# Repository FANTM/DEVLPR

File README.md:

# DEVLPR

## About
 
[FANTM](https://getfantm.com) is creating easy-to-use EMG (muscle-based) interfaces for you and your computer. The DEVLPR is an Arduino shield that will make it so that you too can start playing around with EMG and all of the possibilities it opens up, whether it be for games, robotics, or something we've never thought of. Once we have the hardware in a functional state we plan on adding software libraries to make the device plug-and-play with Arduino and make it easy for the DEVLPR to be integrated into other projects. 

We're just two engineers who have a passion for new tech and Open Source, so share and build away!

## Disclaimer
This hardware is a major work in progress right now. We are still mid development cycle, and the board in its current state likely does not work. Once it is in a stable state we will tag a release but until then it's going to be frequently changing (and improving).

## Getting Started
This library relies on digikeys KiCAD symbol/footprint library, and they have been included as a submodule. This means when cloning with `git clone --recurse-submodules https://github.com/FANTM/DEVLPR`. If something goes wrong, the [git submodules documentation](https://git-scm.com/book/en/v2/Git-Tools-Submodules) is always helpful.

## License Information
This is an Open Source project and as such is licensed under CC. 

  <br />This work is licensed under a <a rel="license" href="http://creativecommons.org/licenses/by-sa/4.0/">Creative Commons Attribution-ShareAlike 4.0 International License</a>.

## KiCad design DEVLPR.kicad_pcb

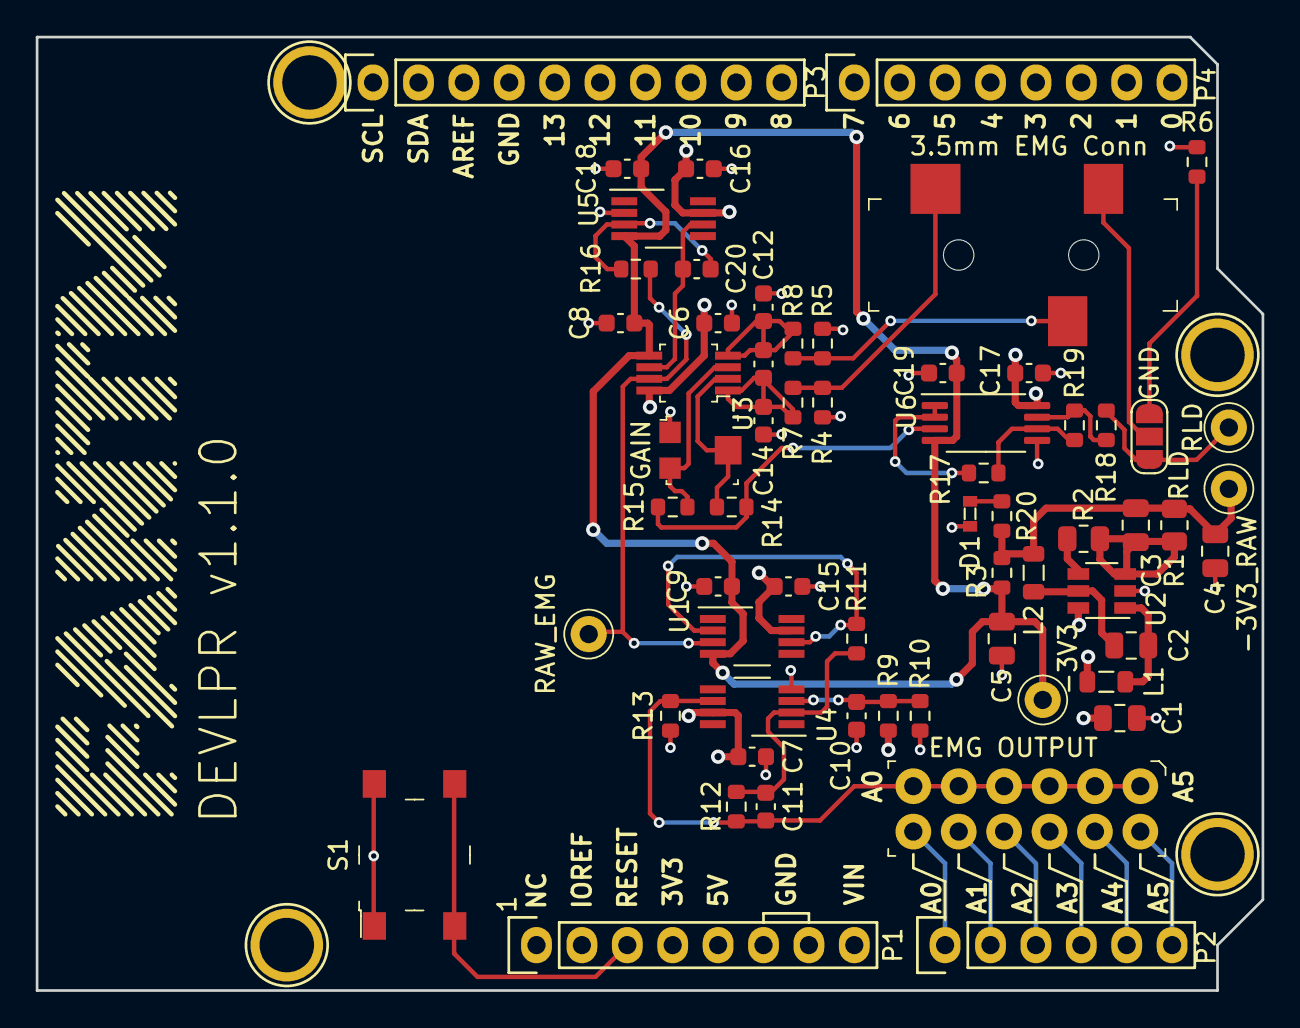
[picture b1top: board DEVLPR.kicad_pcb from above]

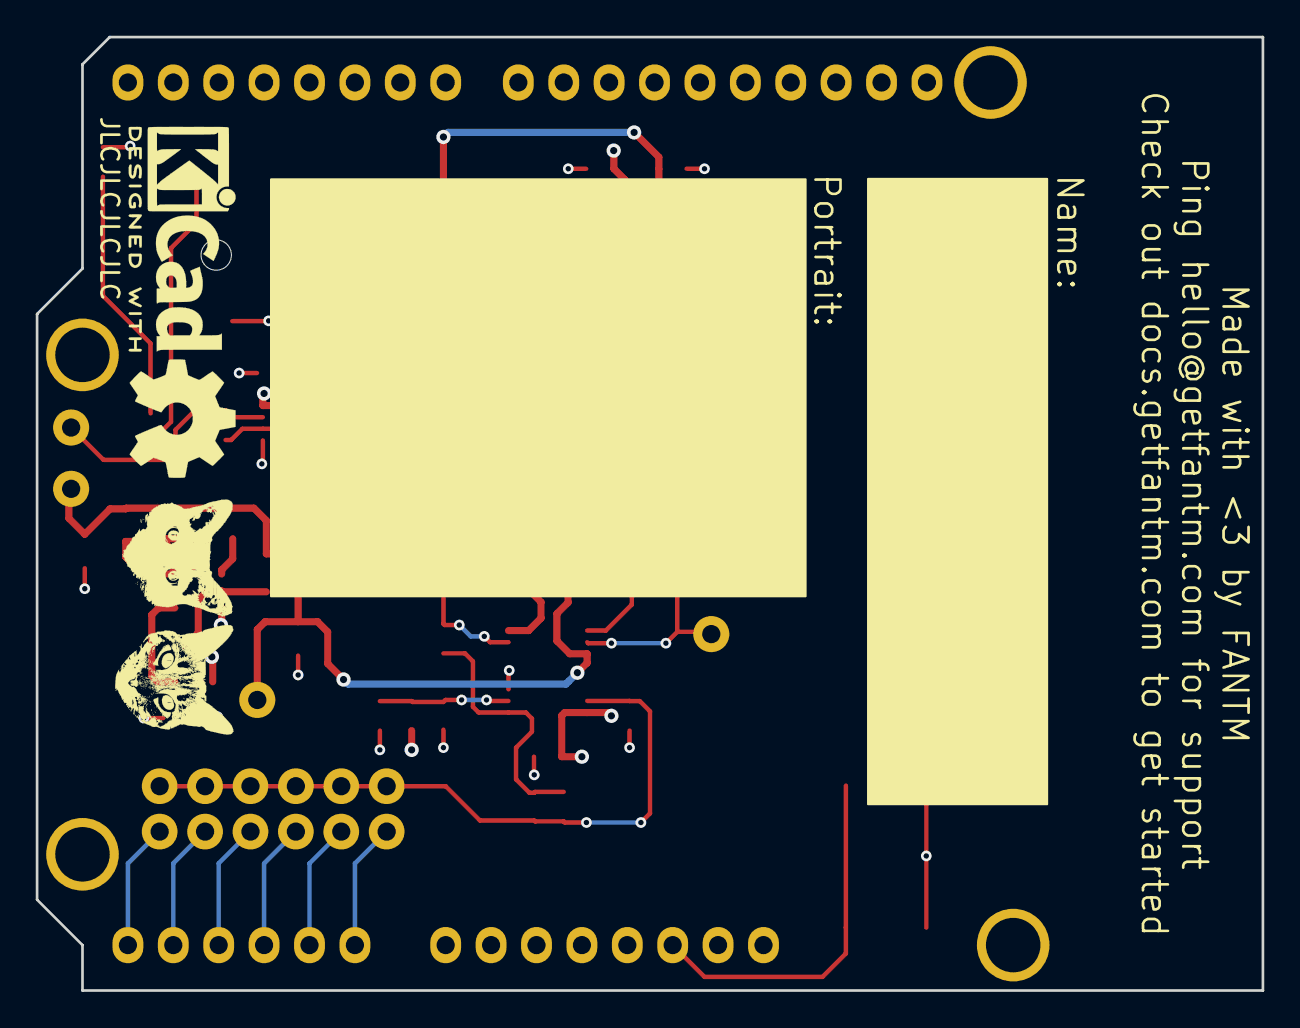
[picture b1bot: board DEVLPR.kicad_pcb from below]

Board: 4 copper layers, 68.6 x 53.3 mm, 72 parts (6 on the bottom side), 36 nets.

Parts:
C1, C2: 1uF; C_0805_2012Metric
C3: 22pF; C_0805_2012Metric
C4: 4.7uF; C_0805_2012Metric
C5: 10uF; C_0805_2012Metric
C6, C7, C8, C9, C15, C16, C17, C18, C19: 0.1uF; C_0603_1608Metric
C10, C20: 1uF; C_0603_1608Metric
C11: 4700pF; C_0603_1608Metric
C12, C14: 2.2pF; C_0603_1608Metric
C13: 10pF; C_0603_1608Metric
CON1: SJ-3523-SMT-TR; Switch_Slide_11.6x4mm_SJ-3523-SMT
D1: GREEN LED; 0603
J1: EMG OUTPUT; PinHeader_6x2_P2.54mm_Horizontal
JP1: RLD_SEL; SolderJumper-3_P1.3mm_Open_RoundedPad1.0x1.5mm_NumberLabels
L1, L2: 10uH; L_0805_2012Metric
P1: Power; Socket_Strip_Arduino_1x08
P2: Analog; Socket_Strip_Arduino_1x06
P3: Digital; Socket_Strip_Arduino_1x10
P4: Digital; Socket_Strip_Arduino_1x08
P5, P6, P7, P8: CONN_01X01; Arduino_1pin
POT1: GAIN; Trimpot_3.8mmx3.6mm_TC33X-2-103E
R1: 267k; R_0805_2012Metric
R2: 102k; R_0805_2012Metric
R3: 249; R_0603_1608Metric
R4, R5: 47k; R_0603_1608Metric
R6, R7, R8, R16, R18, R19: 100k; R_0603_1608Metric
R9: 68k; R_0603_1608Metric
R10, R11, R13, R17: 10k; R_0603_1608Metric
R12: 28.7k; R_0603_1608Metric
R14, R15: 470; R_0603_1608Metric
R20: 1k; R_0603_1608Metric
S1: PTS645SM43SMTR92_LFS; Switch_Tactile_SMD_6x6mm_PTS645
S2: Linus; linus_xsm
S3: Sinclair; sin_ham_bitmap_sm
S4: Kicad; KiCad-Logo2_5mm_SilkScreen
S5: OSHW; OSHW-Symbol_6.7x6mm_SilkScreen
S6: Portrait; portait
S7: Name; name
TP1: -3V3_RAW; Test_Point_D1.02mm
TP2: -3V3; Test_Point_D1.02mm
TP3: RAW_EMG; Test_Point_D1.02mm
TP4: RLD; Test_Point_D1.02mm
U1, U4, U5: OPA187IDR; VSSOP-8_3.0x3.0mm_P0.65mm
U2: LT3462A; TSOT-23-6
U3: INA821IDGKT; TSSOP-8_W3mm
U6: OPA2375IPWR; TSSOP-8_4.4x3mm_P0.65mm

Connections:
+3V3: C1.1, C6.2, C7.2, C15.2, C16.2, C17.2, L1.1, P1.4, R9.1, U1.7, U2.6, U3.8, U4.7, U5.7, U6.8
-3V3: C5.1, C8.2, C9.2, C18.2, C19.2, R3.1, TP2.1, U1.4, U3.5, U5.4, U6.4
/-3V3 Source/-3V3_D: C2.1, L2.1, U2.5
/-3V3 Source/-3V3_FB: C3.2, R1.2, R2.2, U2.3
/-3V3 Source/-3V3_RAW: C3.1, C4.1, L2.2, R1.1, R3.2, R20.1, TP1.1
/-3V3 Source/-3V3_SDREF: R2.1, U2.4
/-3V3 Source/-3V3_SW: C2.2, L1.2, U2.1
/A0: J1.12, P2.1
/A1: J1.10, P2.2
/A2: J1.8, P2.3
/A3: J1.6, P2.4
/A4(SDA): J1.4, P2.5
/A5(SCL): J1.2, P2.6
/EMG Amplifiers/BUFF_FDBK: R11.2, U1.2, U1.6
/EMG Amplifiers/BUFF_MID: C11.1, R11.1, R12.2, U4.2
/EMG Amplifiers/EMG_INSTR: R16.2, TP3.1, U1.3, U3.7
/EMG Amplifiers/GND_REF: JP1.3, R6.1
/EMG Amplifiers/INA_N: C13.1, C14.2, R7.2, U3.1
/EMG Amplifiers/INA_P: C12.1, C13.2, R8.2, U3.4
/EMG Amplifiers/INA_REF: C20.1, U3.6, U5.6
/EMG Amplifiers/REF_-: C20.2, R16.1, U5.3
/EMG Amplifiers/RG1: POT1.2, R14.2, U3.2
/EMG Amplifiers/RG2: POT1.3, R15.1, U3.3
/EMG Amplifiers/RLD: JP1.1, R18.2, TP4.1
/EMG Amplifiers/RLD_IN: R14.1, R15.2, U6.3
/EMG Amplifiers/RLD_IN2_-: R17.1, R19.2, U6.6
/EMG Amplifiers/RLD_MID: R17.2, U6.1, U6.2
/EMG Amplifiers/RLD_OUT2: R18.1, R19.1, U6.7
/EMG Amplifiers/V_SHIFT: C10.2, R9.2, R10.1, U4.3
/EMG_GND: CON1.1, JP1.2
/EMG_N: CON1.2, R4.2, R7.1
/EMG_OUT: C11.2, J1.1, J1.3, J1.5, J1.7, J1.9, J1.11, R12.1, R13.1, U4.6
/EMG_P: CON1.3, R5.2, R8.1
/Reset: P1.3, S1.3, S1.4
GND: C1.2, C4.2, C5.2, C6.1, C7.1, C8.1, C9.1, C10.1, C12.2, C14.1, C15.1, C16.1, C17.1, C18.1, C19.1, D1.1, P1.6, P1.7, P3.4, POT1.1, R4.1, R5.1, R6.2, R10.2, R13.2, S1.1, S1.2, U2.2, U4.4, U5.2, U6.5
unnamed: D1.2, R20.2

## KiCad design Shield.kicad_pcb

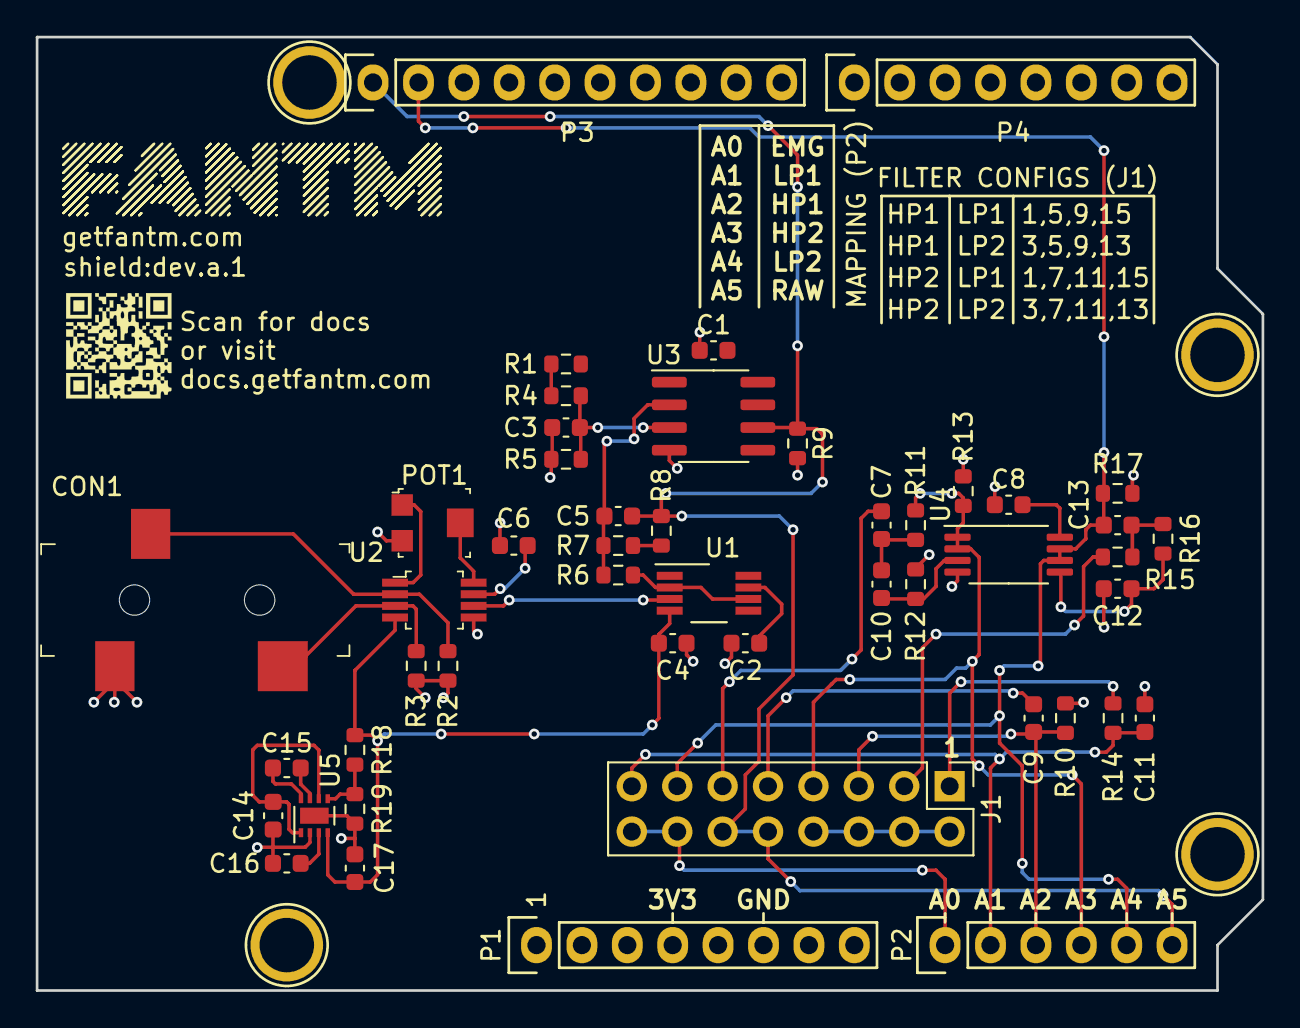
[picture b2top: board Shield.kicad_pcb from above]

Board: 2 copper layers, 68.6 x 53.3 mm, 52 parts (0 on the bottom side), 32 nets.

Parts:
C1, C2, C4, C6, C8: 0.1uF; C_0603_1608Metric
C3, C15: 1uF; C_0603_1608Metric
C5: 43pF; C_0603_1608Metric
C7, C9, C10: 0.15uF; C_0603_1608Metric
C11, C12, C13: 0.033uF; C_0603_1608Metric
C14, C16: 4.7uF; C_0603_1608Metric
C17: 2.2uF; C_0603_1608Metric
CON1: SJ-3523-SMT-TR; Switch_Slide_11.6x4mm_SJ-3523-SMT
J1: Conn_02x08_Row_Letter_Last; PinHeader_2x08_P2.54mm_Vertical
P1: Power; Socket_Strip_Arduino_1x08
P2: Analog; Socket_Strip_Arduino_1x06
P3: Digital; Socket_Strip_Arduino_1x10
P4: Digital; Socket_Strip_Arduino_1x08
P5, P6, P7, P8: CONN_01X01; Arduino_1pin
POT1: TC33X-2-103E; Trimpot_3.8mmx3.6mm_TC33X-2-103E
R1, R7: 33k; R_0603_1608Metric
R2, R3: 47k; R_0603_1608Metric
R4: 3.9k; R_0603_1608Metric
R5, R9, R13, R14, R15, R16, R17: 10k; R_0603_1608Metric
R6: 39k; R_0603_1608Metric
R8: 2.7k; R_0603_1608Metric
R10, R11, R12, R19: 100k; R_0603_1608Metric
R18: 309k; R_0603_1608Metric
U1: OPA140DGK; VSSOP-8_3.0x3.0mm_P0.65mm
U2: INA333AIDGKR; TSSOP-8_W3mm
U3: OPA376xxD; SOIC-8_3.9x4.9mm_P1.27mm
U4: TLV9002IPWR; TSSOP-8_4.4x3mm_P0.65mm
U5: LM27761; WSON-8-1EP_2x2mm_P0.5mm_EP0.9x1.6mm

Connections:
+5V: C1.2, C2.2, C6.2, C8.2, C14.2, P1.5, R1.2, U1.7, U2.7, U3.7, U4.8, U5.1, U5.6
-5V: C4.2, C17.2, R18.2, U1.4, U2.4, U5.4
/A0: J1.14, J1.16, P2.1
/A1: C11.2, J1.15, P2.2, R14.2
/A2: C9.1, J1.5, P2.3, R10.1
/A3: J1.7, P2.4, R11.1, R13.2, U4.1, U4.2
/A4(SDA): C13.2, J1.13, P2.5, P3.2, R17.2, U4.6, U4.7
/A5(SCL): C5.1, J1.10, J1.12, P2.6, P3.1, R8.1, R9.1, U3.6
/EMG Amplifiers/EMG_INSTR: U1.3, U2.6
/EMG Amplifiers/FIRST_ORDER_HP: C9.2, J1.9
/EMG Amplifiers/FIRST_ORDER_LP: J1.1, R14.1
/EMG Amplifiers/HP: J1.2, J1.4, J1.6, J1.8
/EMG Amplifiers/HP_2_+: C10.1, R12.1, U4.3
/EMG Amplifiers/HP_2_MID: C7.1, C10.2, R11.2
/EMG Amplifiers/LP_2_+: C12.2, R16.2, U4.5
/EMG Amplifiers/LP_2_MID: C13.1, R15.2, R16.1
/EMG Amplifiers/SECOND_ORDER_HP: C7.2, J1.11
/EMG Amplifiers/SECOND_ORDER_LP: J1.3, R15.1
/EMG_N: CON1.3, R2.2, U2.2
/EMG_P: CON1.2, R3.2, U2.3
GND: C1.1, C2.1, C3.1, C4.1, C6.1, C8.1, C11.1, C12.1, C14.1, C16.1, C17.1, CON1.1, P1.6, P1.7, P3.4, POT1.3, R2.1, R3.1, R5.2, R9.2, R10.2, R12.2, R13.1, R17.1, R19.2, U2.5, U3.4, U4.4, U5.2, U5.9
unnamed: C3.2, R4.1, R5.1, U3.3
unnamed: C5.2, R6.1, R7.2, U3.2
unnamed: C15.1, U5.7
unnamed: C15.2, U5.8
unnamed: C16.2, U5.3
unnamed: POT1.1, U2.1
unnamed: POT1.2, U2.8
unnamed: R1.1, R4.2
unnamed: R6.2, U1.2, U1.6
unnamed: R7.1, R8.2
unnamed: R18.1, R19.1, U5.5

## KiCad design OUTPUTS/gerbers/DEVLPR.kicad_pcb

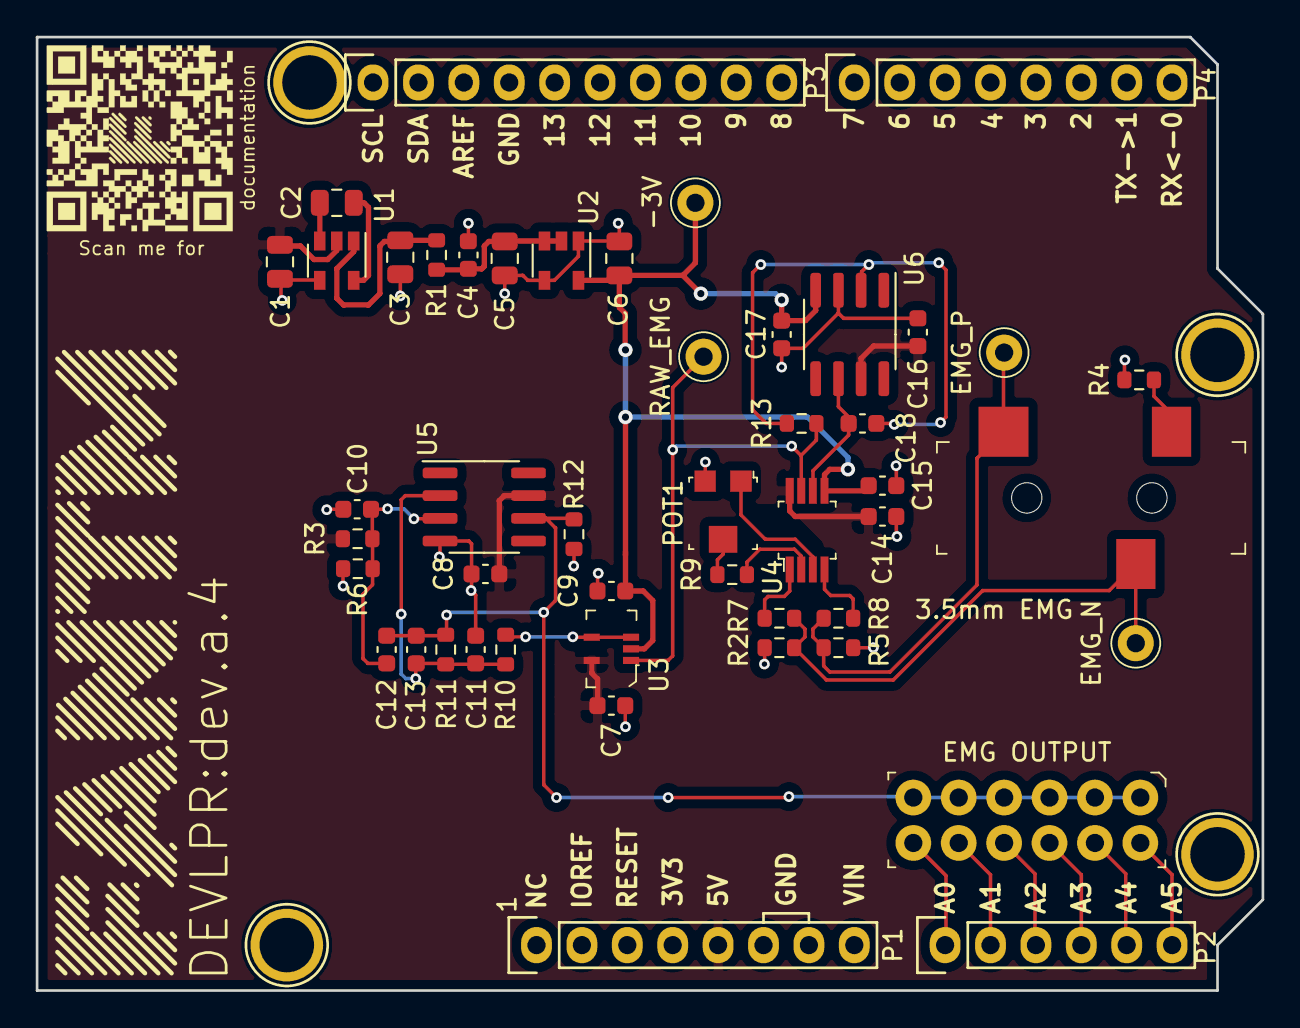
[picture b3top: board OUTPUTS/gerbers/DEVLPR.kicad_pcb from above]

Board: 2 copper layers, 68.6 x 53.3 mm, 52 parts (0 on the bottom side), 28 nets.

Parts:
C1, C2, C3: 3.3uF; C_0805_2012Metric
C4, C7, C8, C9, C14, C15, C16, C17: 0.1uF; C_0603_1608Metric
C5, C6: 1uF; C_0805_2012Metric
C10, C18: 1uF; C_0603_1608Metric
C11, C12, C13: 4700pF; C_0603_1608Metric
CON1: 3.5mm EMG; Switch_Slide_11.6x4mm_SJ-3523-SMT
J1: EMG OUTPUT; PinHeader_6x2_P2.54mm_Horizontal
P1: Power; Socket_Strip_Arduino_1x08
P2: Analog; Socket_Strip_Arduino_1x06
P3: Digital; Socket_Strip_Arduino_1x10
P4: Digital; Socket_Strip_Arduino_1x08
P5, P6, P7, P8: CONN_01X01; Arduino_1pin
POT1: GAIN; Trimpot_3.8mmx3.6mm_TC33X-2-103E
R1: 249; R_0603_1608Metric
R2, R5: 47k; R_0603_1608Metric
R3: 43.2k; R_0603_1608Metric
R4, R7, R8, R13: 100k; R_0603_1608Metric
R6: 1k; R_0603_1608Metric
R9: 470; R_0603_1608Metric
R10: 3.3k; R_0603_1608Metric
R11: 69.8k; R_0603_1608Metric
R12: 10k; R_0603_1608Metric
TP1: EMG_N; Test_Point_D1.02mm
TP2: EMG_P; Test_Point_D1.02mm
TP3: -3V; Test_Point_D1.02mm
TP4: RAW_EMG; Test_Point_D1.02mm
U1: TPS60402; SOT-23-5
U2: MAX1735; SOT-23-5
U3: OPA375DCK; SC-70-5
U4: INA819IDGK; TSSOP-8_W3mm
U5, U6: OPA376xxD; SOIC-8_3.9x4.9mm_P1.27mm

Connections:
+5V: C1.2, C7.2, C8.2, C14.2, C16.2, P1.5, R3.1, U1.2, U3.5, U4.8, U5.7, U6.7
-3V: C6.2, C9.2, C15.2, C17.2, TP3.1, U2.5, U3.2, U4.5, U6.4
/-5V Source/Cfly+: C2.2, U1.5
/-5V Source/Cfly-: C2.1, U1.3
/-5V Source/INV_OUT: C3.2, R1.2, U1.1
/-5V Source/LDO_IN: C4.2, C5.2, R1.1, U2.2, U2.3
/A0: J1.12, P2.1
/A1: J1.10, P2.2
/A2: J1.8, P2.3
/A3: J1.6, P2.4
/A4(SDA): J1.4, P2.5
/A5(SCL): J1.2, P2.6
/EMG Amplifiers/BUFFER_FDBK: R10.2, U3.3, U3.4
/EMG Amplifiers/BUFFER_OUT: C11.2, C13.1, R10.1, R11.2, U5.2
/EMG Amplifiers/EMG_INSTR: R13.2, TP4.1, U3.1, U4.7
/EMG Amplifiers/INA_N: R7.2, U4.1
/EMG Amplifiers/INA_P: R8.2, U4.4
/EMG Amplifiers/INA_REF: C18.1, U4.6, U6.6
/EMG Amplifiers/REF_-: C18.2, R13.1, U6.2
/EMG Amplifiers/RG_1: R9.2, U4.2
/EMG Amplifiers/RG_2: POT1.1, U4.3
/EMG Amplifiers/V_SHIFT: C10.2, C12.1, R3.2, R6.1, U5.3
/EMG_GND: CON1.1, R4.1
/EMG_N: CON1.3, R2.2, R7.1, TP1.1
/EMG_OUT: C12.2, C13.2, J1.1, J1.3, J1.5, J1.7, J1.9, J1.11, R11.1, R12.1, U5.6
/EMG_P: CON1.2, R5.2, R8.1, TP2.1
GND: C1.1, C3.1, C4.1, C5.1, C6.1, C7.1, C8.1, C9.1, C10.1, C11.1, C14.1, C15.1, C16.1, C17.1, P1.6, P1.7, P3.4, POT1.3, R2.1, R4.2, R5.1, R6.2, R12.2, U1.4, U2.1, U2.4, U5.4, U6.3
unnamed: POT1.2, R9.1

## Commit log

2021-04-01 Initial commit with current progress
2021-04-01 Fixed naming and cleaned up libraries
2021-04-07 Adding the LP filter to the level shifter
2021-04-08 Finalized rev dev.a.2 with improved filtering, power supply design, and silkscreen
2021-04-22 Major overhaul given chip shortage. Completely redid the power supply, and refined the amps for the EMG to give better gain and use the full output range
2021-04-22 Fixed SPI signal naming convention to new OSHWA proposal
2021-05-07 Finished rev dev.a.4 with safety improvements, better gain settings, and dc offset removal
2021-06-23 Stupidly named the voltage source and then didn't change it when the V changed
2022-01-05 Created v1.1 of the DEVLPR, adding RLD
